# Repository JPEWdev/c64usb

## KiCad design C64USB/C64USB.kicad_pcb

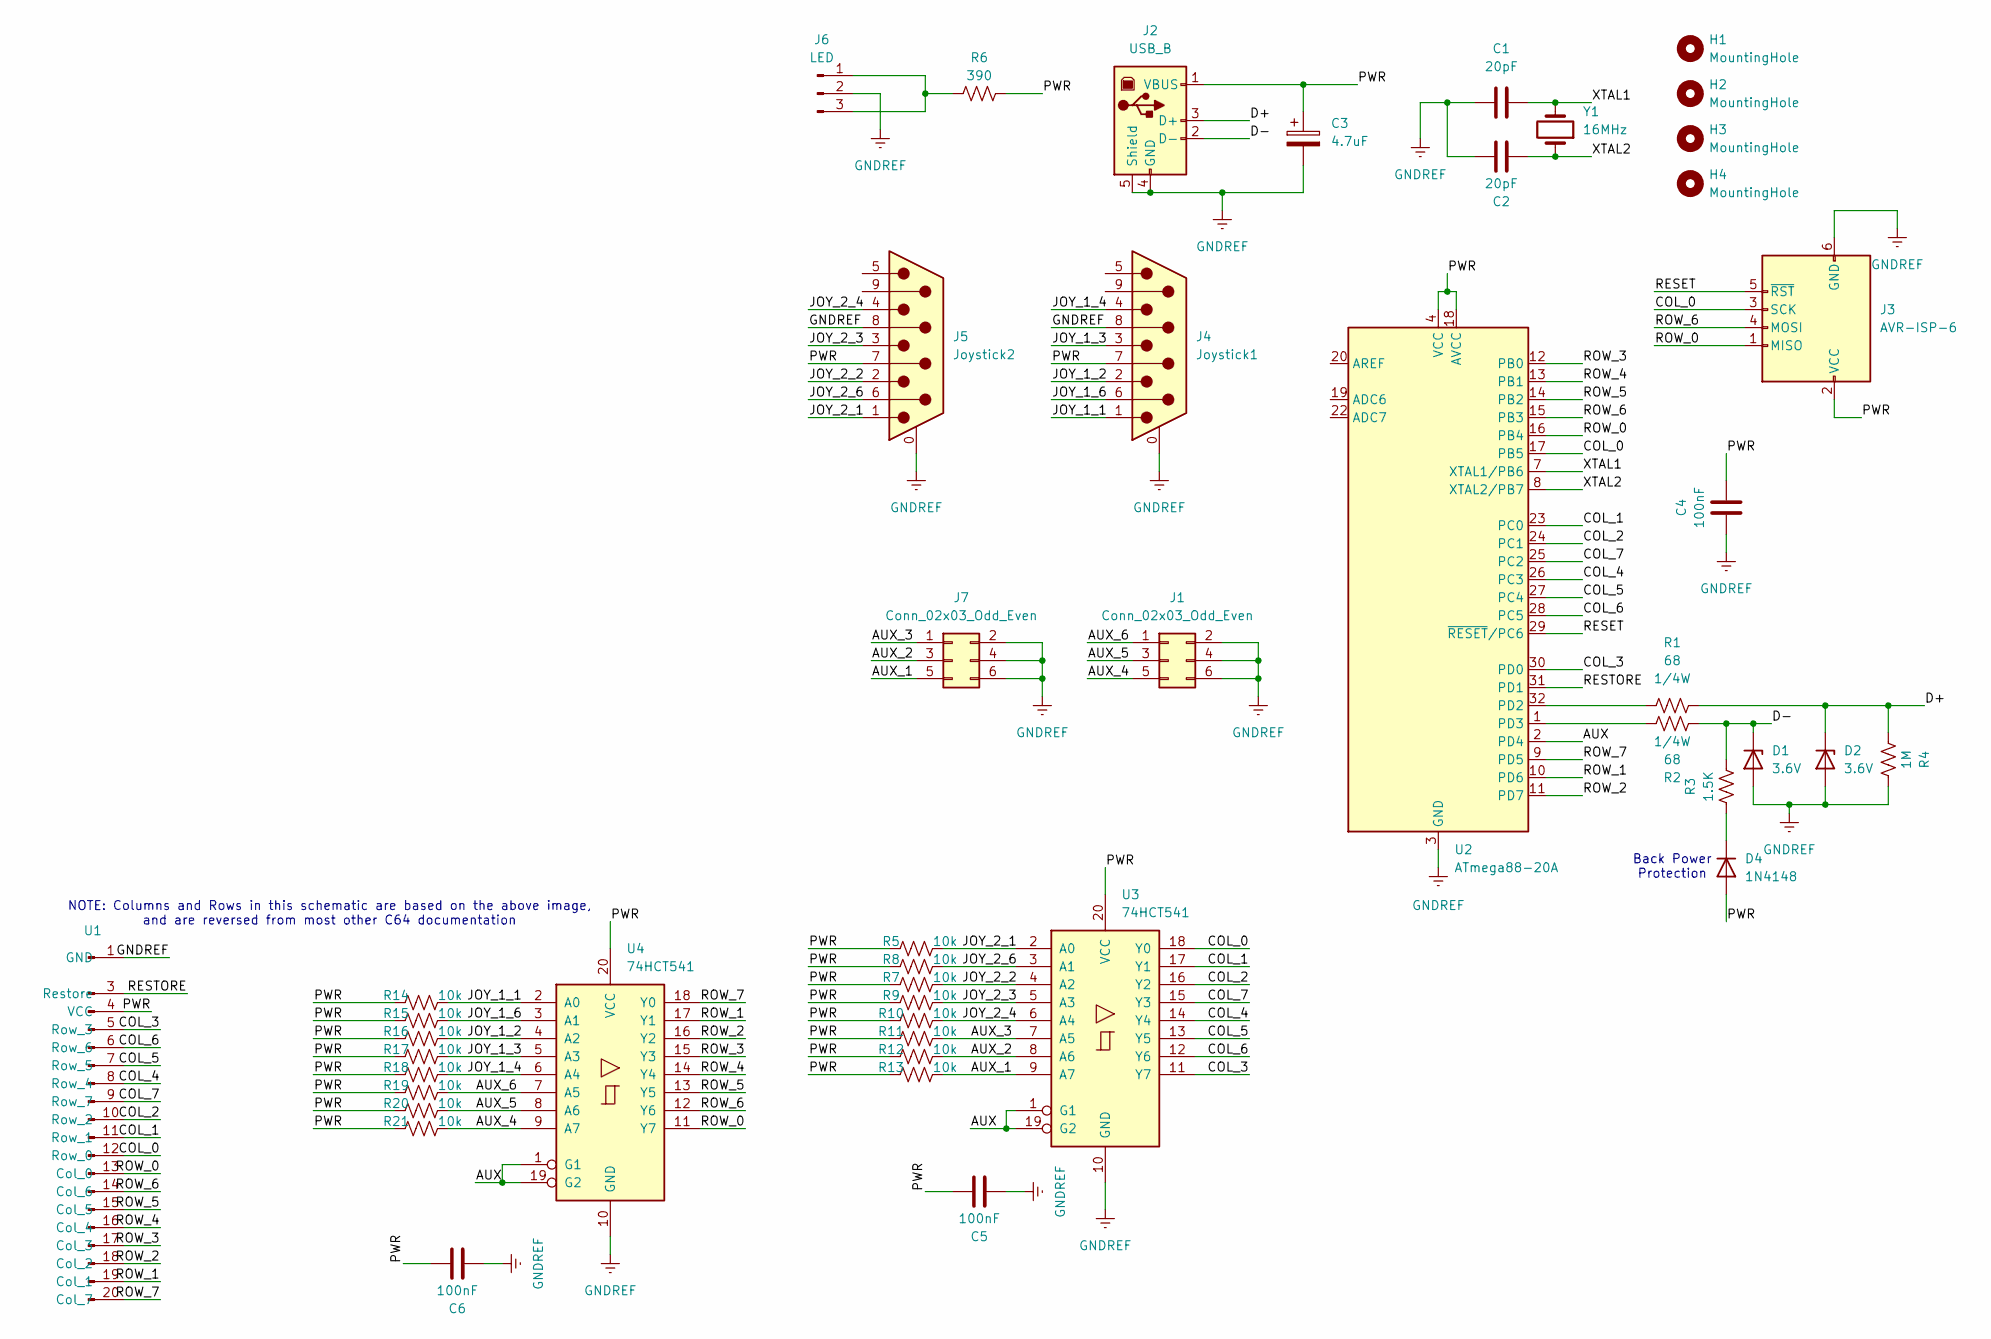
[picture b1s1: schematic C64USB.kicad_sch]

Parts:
C1, C2: 20pF; C_0603_1608Metric_Pad1.08x0.95mm_HandSolder
C3: 4.7uF; CP_Radial_D5.0mm_P2.50mm
C4, C5, C6: 100nF; C_0603_1608Metric_Pad1.08x0.95mm_HandSolder
D1, D2: 3.6V; D_SOD-123
D4: 1N4148; D_SOD-123
H1, H2, H3, H4: MountingHole; MountingHole_3.2mm_M3_Pad_TopBottom
J1, J7: Conn_02x03_Odd_Even; PinHeader_2x03_P2.54mm_Vertical
J2: USB_B; USB_B_Lumberg_2411_02_Horizontal
J3: AVR-ISP-6; PinHeader_2x03_P2.54mm_Vertical
J4: Joystick1; DSUB-9_Male_Horizontal_P2.77x2.84mm_EdgePinOffset7.70mm_Hou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
J5: Joystick2; DSUB-9_Male_Horizontal_P2.77x2.84mm_EdgePinOffset7.70mm_Hou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
J6: LED; PinHeader_1x03_P2.54mm_Vertical
R1, R2: 68; R_0603_1608Metric_Pad0.98x0.95mm_HandSolder
R3: 1.5K; R_0603_1608Metric_Pad0.98x0.95mm_HandSolder
R4: 1M; R_0603_1608Metric_Pad0.98x0.95mm_HandSolder
R5, R7, R8, R9, R10, R11, R12, R13, R14, R15, R16, R17, R18, R19, R20, R21: 10k; R_0603_1608Metric_Pad0.98x0.95mm_HandSolder
R6: 390; R_0603_1608Metric_Pad0.98x0.95mm_HandSolder
U1: C64_Keyboard_Header
U2: ATmega88-20A; TQFP-32_7x7mm_P0.8mm
U3, U4: 74HCT541; SOIC-20W_7.5x12.8mm_P1.27mm
Y1: 16MHz; Crystal_HC49-U_Vertical

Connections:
/AUX: U2.2 (PD4), U3.1 (G1), U3.19 (G2), U4.1 (G1), U4.19 (G2)
/AUX_1: J7.5, R13.2, U3.9 (A7)
/AUX_2: J7.3, R12.2, U3.8 (A6)
/AUX_3: J7.1, R11.2, U3.7 (A5)
/AUX_4: J1.5, R21.2, U4.9 (A7)
/AUX_5: J1.3, R20.2, U4.8 (A6)
/AUX_6: J1.1, R19.2, U4.7 (A5)
/COL_0: J3.3 (SCK), U1.12 (Row_0), U2.17 (PB5), U3.18 (Y0)
/COL_1: U1.11 (Row_1), U2.23 (PC0), U3.17 (Y1)
/COL_2: U1.10 (Row_2), U2.24 (PC1), U3.16 (Y2)
/COL_3: U1.5 (Row_3), U2.30 (PD0), U3.11 (Y7)
/COL_4: U1.8 (Row_4), U2.26 (PC3), U3.14 (Y4)
/COL_5: U1.7 (Row_5), U2.27 (PC4), U3.13 (Y5)
/COL_6: U1.6 (Row_6), U2.28 (PC5), U3.12 (Y6)
/COL_7: U1.9 (Row_7), U2.25 (PC2), U3.15 (Y3)
/D+: D2.1 (K), J2.3 (D+), R1.2, R4.2
/D-: D1.1 (K), J2.2 (D-), R2.2, R3.1
/JOY_1_1: J4.1, R14.2, U4.2 (A0)
/JOY_1_2: J4.2, R16.2, U4.4 (A2)
/JOY_1_3: J4.3, R17.2, U4.5 (A3)
/JOY_1_4: J4.4, R18.2, U4.6 (A4)
/JOY_1_6: J4.6, R15.2, U4.3 (A1)
/JOY_2_1: J5.1, R5.2, U3.2 (A0)
/JOY_2_2: J5.2, R7.2, U3.4 (A2)
/JOY_2_3: J5.3, R9.2, U3.5 (A3)
/JOY_2_4: J5.4, R10.2, U3.6 (A4)
/JOY_2_6: J5.6, R8.2, U3.3 (A1)
/PWR: C3.1, C4.1, C5.1, C6.1, D4.2 (A), J2.1 (VBUS), J3.2 (VCC), J4.7, J5.7, R5.1, R6.2, R7.1, R8.1, R9.1, R10.1, R11.1, R12.1, R13.1, R14.1, R15.1, R16.1, R17.1, R18.1, R19.1, R20.1, R21.1, U1.4 (VCC), U2.4 (VCC), U2.6 (VCC), U2.18 (AVCC), U3.20 (VCC), U4.20 (VCC)
/RESET: J3.5 (~RST), U2.29 (~RESET/PC6)
/RESTORE: U1.3 (Restore), U2.31 (PD1)
/ROW_0: J3.1 (MISO), U1.13 (Col_0), U2.16 (PB4), U4.11 (Y7)
/ROW_1: U1.19 (Col_1), U2.10 (PD6), U4.17 (Y1)
/ROW_2: U1.18 (Col_2), U2.11 (PD7), U4.16 (Y2)
/ROW_3: U1.17 (Col_3), U2.12 (PB0), U4.15 (Y3)
/ROW_4: U1.16 (Col_4), U2.13 (PB1), U4.14 (Y4)
/ROW_5: U1.15 (Col_5), U2.14 (PB2), U4.13 (Y5)
/ROW_6: J3.4 (MOSI), U1.14 (Col_6), U2.15 (PB3), U4.12 (Y6)
/ROW_7: U1.20 (Col_7), U2.9 (PD5), U4.18 (Y0)
/XTAL1: C1.2, U2.7 (XTAL1/PB6), Y1.2
/XTAL2: C2.2, U2.8 (XTAL2/PB7), Y1.1
GNDREF: C1.1, C2.1, C3.2, C4.2, C5.2, C6.2, D1.2 (A), D2.2 (A), J1.2, J1.4, J1.6, J2.4 (GND), J2.5 (Shield), J3.6 (GND), J4.0 (PAD), J4.8, J5.0 (PAD), J5.8, J6.2, J7.2, J7.4, J7.6, R4.1, U1.1 (GND), U2.3 (GND), U2.5 (GND), U2.21 (GND), U3.10 (GND), U4.10 (GND)
unnamed: D4.1 (K), R3.2
unnamed: J6.1, J6.3, R6.1
unnamed: R1.1, U2.32 (PD2)
unnamed: R2.1, U2.1 (PD3)

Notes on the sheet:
NOTE: Columns and Rows in this schematic are based on the above image, and are reversed from most other C64 documentation
Back Power Protection

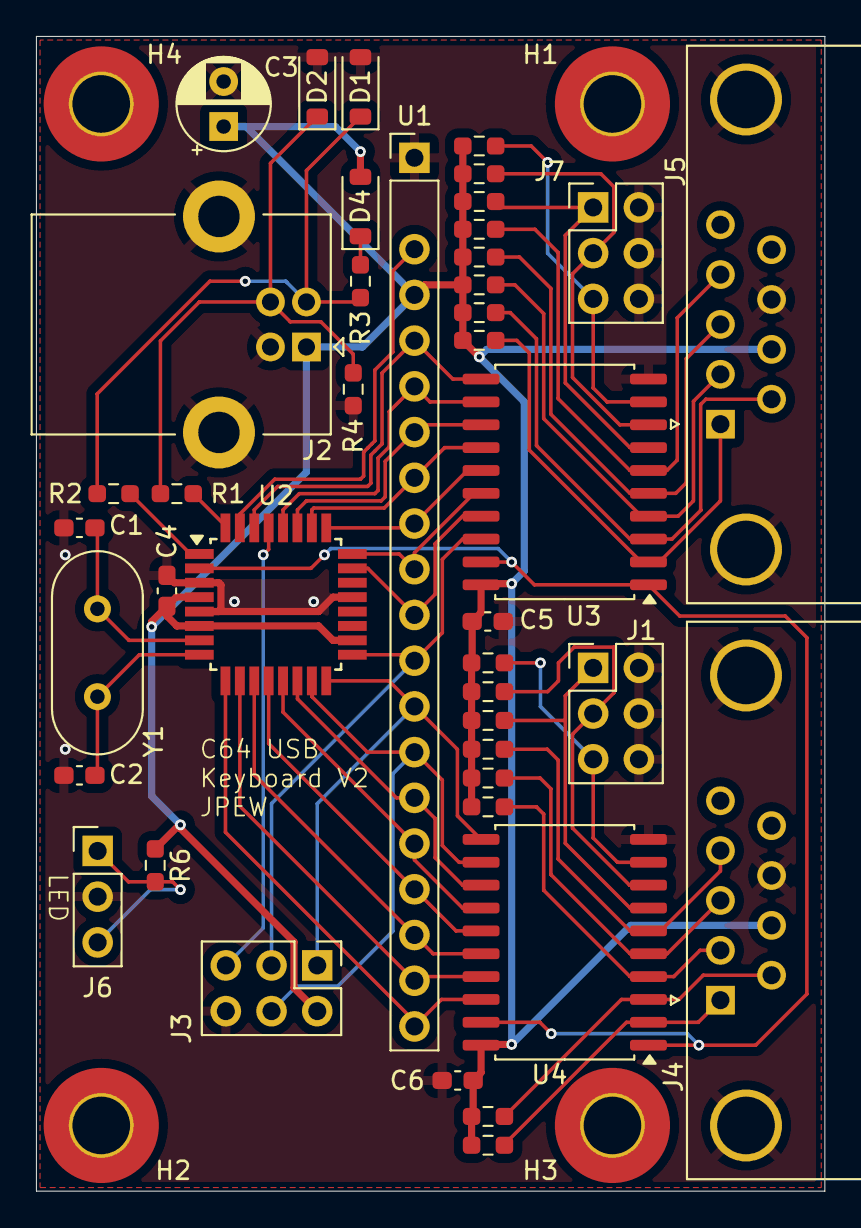
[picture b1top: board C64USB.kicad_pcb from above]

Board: 2 copper layers, 43.8 x 64.2 mm, 46 parts (0 on the bottom side), 45 nets.

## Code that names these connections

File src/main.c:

/*
 * SPDX-License-Identifier MIT License
 *
 * Copyright (c) 2024 Joshua Watt
 */
#include <avr/interrupt.h>
#include <avr/io.h>
#include <avr/wdt.h>
#include <stdbool.h>
#include <string.h>
#include <util/atomic.h>
#include <util/delay.h>

#include "hid_report.h"
#include "keymaps.h"
#include "pin.h"
#include "timer.h"
#include "usb_hid_keys.h"
#include "usbdrv.h"
#include "util.h"

#define KEYBOARD_REPORT_ID (1)
#define POLL_RATE_MS (16)
#define SETTLE_TIME_US (100)

// Settle time must be less than the poll rate and also less than the maximum
// settle time
_Static_assert(SETTLE_TIME_US * 9 <= POLL_RATE_MS * 1000,
               "Settle time is too long");

#define NUM_JOYSTICKS (2)

#define DEBUG_SCAN (0)

#define ROW_0 PIN(B, 4)
#define ROW_1 PIN(D, 6)
#define ROW_2 PIN(D, 7)
#define ROW_3 PIN(B, 0)
#define ROW_4 PIN(B, 1)
#define ROW_5 PIN(B, 2)
#define ROW_6 PIN(B, 3)
#define ROW_7 PIN(D, 5)

#define COL_0 PIN(B, 5)
#define COL_1 PIN(C, 0)
#define COL_2 PIN(C, 1)
#define COL_3 PIN(D, 0)
#define COL_4 PIN(C, 3)
#define COL_5 PIN(C, 4)
#define COL_6 PIN(C, 5)
#define COL_7 PIN(C, 2)

static const struct pin rows[] = {
    ROW_0, ROW_1, ROW_2, ROW_3, ROW_4, ROW_5, ROW_6, ROW_7,
};

_Static_assert(ARRAY_SIZE(rows) == KEY_ROWS, "keymap wrong size");

static const struct pin cols[] = {
    COL_0, COL_1, COL_2, COL_3, COL_4, COL_5, COL_6, COL_7,
};

_Static_assert(ARRAY_SIZE(cols) == KEY_COLS, "keymap wrong size");

static const struct pin aux[] = {
    COL_0, COL_1, COL_2, COL_3, COL_4, COL_5, COL_6, COL_7,
    ROW_0, ROW_1, ROW_2, ROW_3, ROW_4, ROW_5, ROW_6, ROW_7,
};
_Static_assert(ARRAY_SIZE(aux) == KEY_AUX, "Keymap wrong size");

static const struct pin restore_pin = PIN(D, 1);
static const struct pin aux_pin = PIN(D, 4);

#define REPORT_BIT_KEYS (1 + (KEY_AUX))
#define REPORT_BYTE_KEYS (4)

#if REPORT_BIT_KEYS % 8
#define REPORT_BIT_KEY_BYTES ((REPORT_BIT_KEYS / 8) + 1)
#define REPORT_CONST_BITS (8 - (REPORT_BIT_KEYS % 8))
#else
#define REPORT_BIT_KEY_BYTES (REPORT_BIT_KEYS / 8)
#define REPORT_CONST_BITS (0)
#endif

#define REPORT_KEY_BYTES (REPORT_BIT_KEY_BYTES + REPORT_BYTE_KEYS)

static struct hid_report report;

static const struct keymap *const keymap = &vice_keymap;

// Idle rate is in multiples of 4 milliseconds
static uint8_t idle_rate;
static uint32_t last_idle;

/* clang-format off */
PROGMEM static const uint8_t usb_hid_report_descriptor_header[] = {
    0x05, 0x01,                 // Usage Page (Generic Desktop Ctrls)
    0x09, 0x06,                 // Usage (Keyboard)
    0xA1, 0x01,                 // Collection (Application)
    0x85, KEYBOARD_REPORT_ID,   //   Report ID
    0x05, 0x07,                 //   Usage Page (Kbrd/Keypad)
    0x15, 0x00,                 //   Logical Minimum (0)
    0x25, 0x01,                 //   Logical Maximum (1)
    0x75, 0x01,                 //   Report Size (1)
    0x95, REPORT_BIT_KEYS,      //   Report Count
};

PROGMEM static const uint8_t usb_hid_report_descriptor_footer[] = {
    0x81, 0x02,                 //   Input (Data, Variable, Absolute)
    0x75, REPORT_CONST_BITS,    //   Report Size
    0x95, 0x01,                 //   Report Count (1)
    0x81, 0x03,                 //   Input (Constant)
    0x95, REPORT_BYTE_KEYS,     //   Report Count
    0x75, 0x08,                 //   Report Size (8)
    0x15, 0x00,                 //   Logical Minimum (0)
    0x25, 0xFF,                 //   Logical Maximum (0xFF)
    0x05, 0x07,                 //   Usage Page (Key codes)
    0x19, 0x00,                 //   Usage Minimum (0)
    0x29, 0xFF,                 //   Usage Maximum (0xFF)
    0x81, 0x00,                 //   Input (Data, Array)
    0xC0,                       // End Collection
};
/* clang-format on */

char usbHidReportDescriptor[sizeof(usb_hid_report_descriptor_header) +
                            (2 * REPORT_BIT_KEYS) +
                            sizeof(usb_hid_report_descriptor_footer)];

_Static_assert(sizeof(usbHidReportDescriptor) ==
                   USB_CFG_HID_REPORT_DESCRIPTOR_LENGTH,
               "HID report is wrong size");

#if DEBUG_SCAN
static void set_debug_leds(uint8_t leds) {
  for (uint8_t i = 0; i < KEY_ROWS; i++) {
    pin_set(&rows[i], (leds & 1) ? PIN_OUTPUT_LO : PIN_HIGH_Z);
    leds >>= 1;
  }
}
#else
#define set_debug_leds(leds)
#endif

static void reset(void) {
  cli();
  wdt_enable(WDTO_15MS);
  while (true)
    ;
}

#define add_keymap(k)                                                          \
  do {                                                                         \
    *(ptr++) = 0x09;                                                           \
    *(ptr++) = pgm_read_byte(&(k));                                            \
  } while (0)
static void init_hid_report() {
  char *ptr = usbHidReportDescriptor;

  memcpy_P(ptr, usb_hid_report_descriptor_header,
           sizeof(usb_hid_report_descriptor_header));
  ptr += sizeof(usb_hid_report_descriptor_header);

  for (uint8_t i = 0; i < KEY_AUX; i++) {
    add_keymap(keymap->aux[i]);
  }
  add_keymap(keymap->restore);

  memcpy_P(ptr, usb_hid_report_descriptor_footer,
           sizeof(usb_hid_report_descriptor_footer));
  ptr += sizeof(usb_hid_report_descriptor_footer);

  // Check report size
  if (ptr != usbHidReportDescriptor + sizeof(usbHidReportDescriptor)) {
    reset();
  }
}

static void poll_loop() {
  uint32_t now = get_milliseconds();

  wdt_reset();
  usbPoll();

  if (usbInterruptIsReady() &&
      (report.changed || (idle_rate && (now - last_idle >= idle_rate * 4)))) {
    report.changed = false;
    usbSetInterrupt(report.data, report.len);
    last_idle = now;
  }
}

static void read_settle() {
  poll_loop();
  _delay_us(SETTLE_TIME_US);
}

static void read_inputs() {
  struct hid_report r;

  // Make a copy of the report so we don't have to keep interrupts disabled
  // while sleeping
  ATOMIC_BLOCK(ATOMIC_RESTORESTATE) { r = report; }

  hid_report_start(&r);
  hid_report_add_byte(&r, KEYBOARD_REPORT_ID);

  for (uint8_t col = 0; col < KEY_COLS; col++) {
    pin_set(&cols[col], PIN_INPUT);
  }

  for (uint8_t row = 0; row < KEY_ROWS; row++) {
    pin_set(&rows[row], PIN_INPUT);
  }
  pin_set(&restore_pin, PIN_INPUT);

  // Read auxiliary inputs
  pin_set(&aux_pin, PIN_OUTPUT_LO);
  read_settle();
  for (uint8_t i = 0; i < KEY_AUX; i++) {
    hid_report_add_bit(&r, pin_read(&aux[i]));
  }
  pin_set(&aux_pin, PIN_OUTPUT_HI);

  // Read restore pin
  hid_report_add_bit(&r, pin_read(&restore_pin));

  hid_report_fill_bits(&r, REPORT_CONST_BITS);

  for (uint8_t row = 0; row < KEY_ROWS; row++) {
    pin_set(&rows[row], PIN_HIGH_Z);
  }

  for (uint8_t row = 0; row < KEY_ROWS; row++) {
    pin_set(&rows[row], PIN_OUTPUT_LO);
    read_settle();
    for (uint8_t col = 0; col < KEY_COLS; col++) {
      if (pin_read(&cols[col])) {
        hid_report_add_byte(&r, pgm_read_byte(&keymap->keys[row][col]));
      }
    }
    pin_set(&rows[row], PIN_HIGH_Z);
  }

  for (uint8_t row = 0; row < KEY_ROWS; row++) {
    pin_set(&rows[row], PIN_INPUT);
  }

  hid_report_finish(&r);

  // Update report
  ATOMIC_BLOCK(ATOMIC_RESTORESTATE) { report = r; }
}

int main(void) {
  wdt_enable(WDTO_1S);
  init_hid_report();

  timer_init();

  // Initialize pins
  for (uint8_t col = 0; col < KEY_COLS; col++) {
    pin_init(&cols[col]);
  }
  for (uint8_t row = 0; row < KEY_ROWS; row++) {
    pin_init(&rows[row]);
  }
  pin_init(&aux_pin);
  pin_set(&aux_pin, PIN_OUTPUT_HI);
  pin_init(&restore_pin);
  hid_report_init(&report, REPORT_KEY_BYTES + 1);

  usbInit();
  usbDeviceDisconnect(); /* enforce re-enumeration, do this while interrupts are
                            disabled! */

  /* fake USB disconnect for > 250 ms */
  {
    uint8_t i = 250;
    set_debug_leds(1);
    while (--i) {
      wdt_reset();
      _delay_ms(1);
    }
    set_debug_leds(0);
  }
  usbDeviceConnect();

  sei();
  uint32_t last_key_poll = get_milliseconds();
  last_idle = get_milliseconds();

  while (true) {
    poll_loop();

    uint32_t now = get_milliseconds();

    if (now - last_key_poll >= POLL_RATE_MS) {
      set_debug_leds(0);
      read_inputs();
      set_debug_leds(report.data[3]);
      last_key_poll = now;
    }
  }
}

usbMsgLen_t usbFunctionSetup(uchar data[8]) {
  usbRequest_t const *request = (usbRequest_t const *)data;

  if ((request->bmRequestType & USBRQ_TYPE_MASK) == USBRQ_TYPE_CLASS) {
    if (request->bRequest == USBRQ_HID_GET_REPORT) {
      /* wValue: ReportType (highbyte), ReportID (lowbyte) */
      if (request->wValue.bytes[1] == KEYBOARD_REPORT_ID) {
        report.changed = false;
        usbMsgPtr = report.data;
        return report.len;
      }

    } else if (request->bRequest == USBRQ_HID_GET_IDLE) {
      usbMsgPtr = &idle_rate;
      return 1;

    } else if (request->bRequest == USBRQ_HID_SET_IDLE) {
      idle_rate = request->wValue.bytes[1];
      last_idle = get_milliseconds();
    }
  }
  return 0;
}

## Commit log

2024-12-31 Initial Implementation
    Initial Implementation
2025-01-13 Clamp D- pull up voltage
    Clamps the D- pull up to ~3.3V using the simple technique of two
    1N4148 diodes. Some USB host controllers are sensitive to the D- line
    being pulled up to 5V (even with the 1.5K pull up resistor) and will
    refuse to enumerate the device if it does so. For some reason, the TVS
    diodes are not clamping the output to 3.6V.
    This was particularly noticed when using the board with a Raspberry Pi
2025-01-15 Fix joystick 1 left
    It was incorrectly mapped to HID_KEY_SLASH when HID_KEY_KP_SLASH (the
    keypad slash) was intended.
2025-01-15 Increase settle time
    Increases the settle time to 15 microseconds
2025-01-15 Simplify the HID report structure
    Simplifies the HID report code to use a static 8 byte buffer for the HID
    report, since this appears to be all V-USB can handle (and all we really
    need anyway)
2025-01-17 Read inputs without interrupts disabled
    The code to read the inputs no longer keeps interrupts disabled, which
    means that the settle time can be much longer. In addition, it will now
    run the main polling while waiting for the inputs to settle to make sure
    USB requests are serviced promptly
2025-01-18 Replace micro-USB connector with USB-B
    The micro USB connector is very difficult to solder correctly, so
    replace it with a USB-B connector which should be much easier
2025-01-18 Use custom symbol and footprint for keyboard header
    This one correctly omits the key pin
2025-01-18 Allow more space for keyboard header
2025-01-18 Remove one diode from D-
    After further testing, a single diode is sufficient to allow the device
    to enumerate on the problematic USB controllers. This leads me to
    believe that this means the controller is actually detecting the device
    being back-powered through D-, which makes a lot more sense, and the
    Zener diode is sufficiently clamping the voltage
2025-01-18 Remove debug LED
    The debug LED isn't particularly useful since it's tied to the AUX line
    and I didn't even bother populating it on the prototype board
2025-01-18 Move mounting holes
    Moves the mounting holes to a better position
2025-02-13 Back Power Protection Diode
    Some USB host controller (specifically, the one on the Raspberry Pi 4)
    can detect if a device is being back powered through the D+ line (that
    is, drawing power through D+ when the 5V supply is off), and if so will
    shut down the port. Add a diode on the D+ line to prevent power from
    being drawn through it.
2025-02-13 Use buffer on joystick and aux keys
    There was a problem where joystick or auxiliary key inputs would result
    in keyboard keys being detected when they were not actually pressed.
    While this is accurate to the actual Commodore 64 keyboard and joystick
    input, having it happen on this USB device meant that it could not be
    correctly disambiguated by the emulator. As such, the board is
    redesigned to use a 74HCT541 tri state buffer chip to isolate the
